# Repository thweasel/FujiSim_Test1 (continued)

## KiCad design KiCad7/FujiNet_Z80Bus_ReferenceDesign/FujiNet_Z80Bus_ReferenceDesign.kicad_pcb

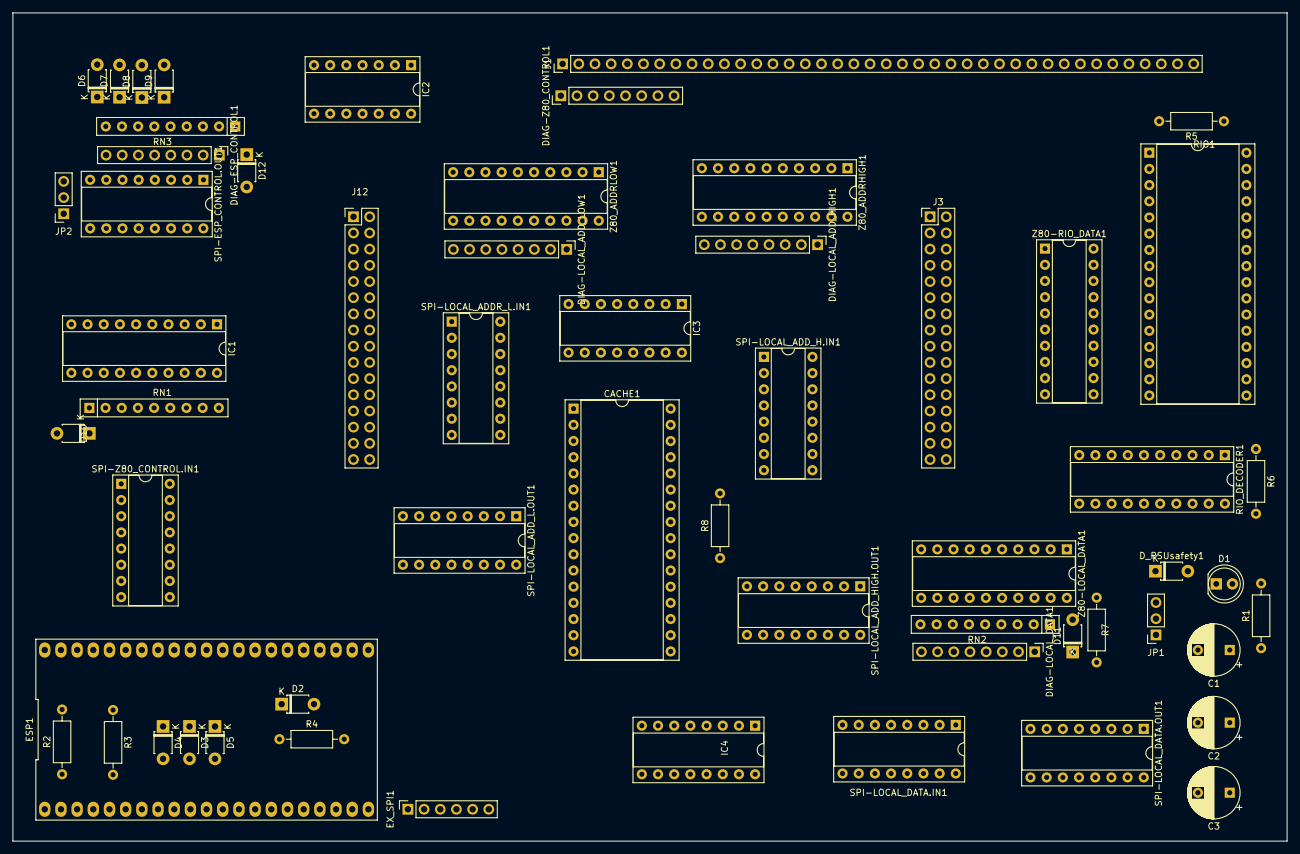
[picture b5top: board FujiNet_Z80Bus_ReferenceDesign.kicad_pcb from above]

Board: 2 copper layers, 200.0 x 130.0 mm, 58 parts (0 on the bottom side), 142 nets, no tracks yet.

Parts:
C1: 10 uf; CP_Radial_D8.0mm_P5.00mm
C2, C3: .1 uf; CP_Radial_D8.0mm_P5.00mm
CACHE1: AS6C1008-55PCN; DIP-32_W15.24mm_Socket
D1: POWER_LED; LED_D5.0mm
D2, D3, D4, D5, D6, D7, D8, D9, D10, D11, D12: 1N4148; D_T-1_P5.08mm_Horizontal
DIAG-ESP_CONTROL1: PinHeader_2.54mm; PinHeader_1x08_P2.54mm_Vertical
DIAG-LOCAL_ADD_HIGH1: PinHeader_2.54mm; PinHeader_1x08_P2.54mm_Vertical
DIAG-LOCAL_ADD_LOW1: PinHeader_2.54mm; PinHeader_1x08_P2.54mm_Vertical
DIAG-LOCAL_DATA1: PinHeader_2.54mm; PinHeader_1x08_P2.54mm_Vertical
DIAG-Z80_CONTROL1: PinHeader_2.54mm; PinHeader_1x08_P2.54mm_Vertical
D_PSUsafety1: 1N4148; D_T-1_P5.08mm_Horizontal
ESP1: FREENOVE_ESP32-WROVER-DEV
EX_SPI1: PinSocket_2.54mm; PinSocket_1x06_P2.54mm_Vertical
IC1: 74HC244N; DIP-20_W7.62mm_Socket
IC2: 74HC32N; DIP-14_W7.62mm_Socket
IC3, IC4: 74HC590N; DIP-16_W7.62mm_Socket
J1: DIAG-HOST_SYSTEM_BUS; PinHeader_1x40_P2.54mm_Vertical
J3, J12: Conn_02x12_Odd_Even; PinHeader_2x16_P2.54mm_Vertical
JP1: PINHD-POWER/RESET; PinSocket_1x03_P2.54mm_Vertical
JP2: PINHD-ADDR_FILTER; PinSocket_1x03_P2.54mm_Vertical
R1: 1K; R_Axial_DIN0207_L6.3mm_D2.5mm_P10.16mm_Horizontal
R2, R3, R4: 22K; R_Axial_DIN0207_L6.3mm_D2.5mm_P10.16mm_Horizontal
R5, R6, R7, R8: 10K; R_Axial_DIN0207_L6.3mm_D2.5mm_P10.16mm_Horizontal
RIO1: AS6C1008-55PCN; DIP-32_W15.24mm_Socket
RIO_DECODER1: 74HC245N; DIP-20_W7.62mm_Socket
RN1: LOCAL_CONTROL_BIAS; R_Array_SIP9
RN2, RN3: 4609M-101-103LF; R_Array_SIP9
SPI-ESP_CONTROL.OUT1: 74595N; DIP-16_W7.62mm_Socket
SPI-LOCAL_ADDR_L.IN1: 74HC165N; DIP-16_W7.62mm_Socket
SPI-LOCAL_ADD_H.IN1: 74HC165N; DIP-16_W7.62mm_Socket
SPI-LOCAL_ADD_HIGH.OUT1: 74595N; DIP-16_W7.62mm_Socket
SPI-LOCAL_ADD_L.OUT1: 74595N; DIP-16_W7.62mm_Socket
SPI-LOCAL_DATA.IN1: 74HC165N; DIP-16_W7.62mm_Socket
SPI-LOCAL_DATA.OUT1: 74595N; DIP-16_W7.62mm_Socket
SPI-Z80_CONTROL.IN1: 74HC165N; DIP-16_W7.62mm_Socket
Z80-LOCAL_DATA1, Z80-RIO_DATA1, Z80_ADDRHIGH1, Z80_ADDRLOW1: 74HC245N; DIP-20_W7.62mm_Socket

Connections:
+5V: C1.1, C2.1, C3.1, CACHE1.32 (VCC), D10.2 (A), D11.2 (A), D12.2 (A), D_PSUsafety1.2 (A), ESP1.20 (+5V), EX_SPI1.5, IC1.20 (VCC), IC2.14 (VCC), IC3.16 (VCC), IC4.16 (VCC), J12.21, R1.1, R2.2, R4.1, R5.1, R6.2, R7.2, R8.2, RIO1.32 (VCC), RIO_DECODER1.20 (VCC), SPI-ESP_CONTROL.OUT1.16 (VCC), SPI-LOCAL_ADDR_L.IN1.16 (VCC), SPI-LOCAL_ADD_H.IN1.16 (VCC), SPI-LOCAL_ADD_HIGH.OUT1.16 (VCC), SPI-LOCAL_ADD_L.OUT1.16 (VCC), SPI-LOCAL_DATA.IN1.16 (VCC), SPI-LOCAL_DATA.OUT1.16 (VCC), SPI-Z80_CONTROL.IN1.16 (VCC), Z80-LOCAL_DATA1.20 (VCC), Z80-RIO_DATA1.20 (VCC), Z80_ADDRHIGH1.20 (VCC), Z80_ADDRLOW1.20 (VCC)
/!ESP_HARDLOCK: IC1.19 (2OE), J12.20
/CACHE_CONTROL.A16: CACHE1.2 (A16), J3.12
/CACHE_CONTROL.CS: CACHE1.22 (CE#), J3.18
/CACHE_CONTROL.DATASTATUS+PERM_Z80_IORQ: IC3.11 (CPC), IC3.13 (CPR), J3.10
/CACHE_CONTROL.OE: CACHE1.24 (OE#), J3.16
/CACHE_CONTROL.WE: CACHE1.29 (WE#), J3.14
/CACHE_DATASTATUS: IC3.12 (~CE), IC3.14 (~OE), IC4.12 (~CE), IC4.14 (~OE), J3.9, R7.1, RIO_DECODER1.14 (B4)
/CACHE_SEL_0: CACHE1.4 (A12), RIO_DECODER1.18 (B0)
/CACHE_SEL_1: CACHE1.28 (A13), RIO_DECODER1.17 (B1)
/CACHE_SEL_2: CACHE1.3 (A14), RIO_DECODER1.16 (B2)
/CACHE_SEL_3: CACHE1.31 (A15), RIO_DECODER1.15 (B3)
/CORE_ESP32-WROVER/ESP_INT: D3.2 (A), D4.2 (A), D5.2 (A), ESP1.3 (GPIO36), R2.1, R3.2
/CORE_ESP32-WROVER/ESP_PULSE: ESP1.11 (GPIO27), IC2.1
/CORE_ESP32-WROVER/ESP_SPI_INT.CE: ESP1.31 (GPIO5), SPI-LOCAL_ADDR_L.IN1.15 (~CE), SPI-LOCAL_ADD_H.IN1.15 (~CE), SPI-LOCAL_DATA.IN1.15 (~CE), SPI-Z80_CONTROL.IN1.15 (~CE)
/CORE_ESP32-WROVER/ESP_SPI_INT.MISO: ESP1.33 (GPIO19), SPI-LOCAL_ADD_H.IN1.7 (~Q7)
/CORE_ESP32-WROVER/ESP_SPI_INT.MOSI: ESP1.39 (GPIO23), SPI-LOCAL_DATA.OUT1.14 (SER)
/CORE_ESP32-WROVER/ESP_SPI_INT.MR: R4.2, SPI-ESP_CONTROL.OUT1.10 (~SRCLR), SPI-LOCAL_ADD_HIGH.OUT1.10 (~SRCLR), SPI-LOCAL_ADD_L.OUT1.10 (~SRCLR), SPI-LOCAL_DATA.OUT1.10 (~SRCLR)
/CORE_ESP32-WROVER/ESP_SPI_INT.OE: ESP1.8 (GPIO33), SPI-ESP_CONTROL.OUT1.13 (~OE), SPI-LOCAL_ADD_HIGH.OUT1.13 (~OE), SPI-LOCAL_ADD_L.OUT1.13 (~OE)
/CORE_ESP32-WROVER/ESP_SPI_INT.PL: ESP1.9 (GPIO25), SPI-LOCAL_ADDR_L.IN1.1 (~PL), SPI-LOCAL_ADD_H.IN1.1 (~PL), SPI-LOCAL_DATA.IN1.1 (~PL), SPI-Z80_CONTROL.IN1.1 (~PL)
/CORE_ESP32-WROVER/ESP_SPI_INT.SCK: ESP1.32 (GPIO18), SPI-ESP_CONTROL.OUT1.11 (SRCLK), SPI-LOCAL_ADDR_L.IN1.2 (CP), SPI-LOCAL_ADD_H.IN1.2 (CP), SPI-LOCAL_ADD_HIGH.OUT1.11 (SRCLK), SPI-LOCAL_ADD_L.OUT1.11 (SRCLK), SPI-LOCAL_DATA.IN1.2 (CP), SPI-LOCAL_DATA.OUT1.11 (SRCLK), SPI-Z80_CONTROL.IN1.2 (CP)
/CORE_ESP32-WROVER/ESP_SPI_INT.STC: ESP1.10 (GPIO26), SPI-ESP_CONTROL.OUT1.12 (RCLK), SPI-LOCAL_ADD_HIGH.OUT1.12 (RCLK), SPI-LOCAL_ADD_L.OUT1.12 (RCLK), SPI-LOCAL_DATA.OUT1.12 (RCLK)
/CORE_ESP32-WROVER/EX_MISO: ESP1.13 (GPIO12), EX_SPI1.3
/CORE_ESP32-WROVER/EX_MOSI: ESP1.15 (GPIO13), EX_SPI1.4
/CORE_ESP32-WROVER/EX_SCK: ESP1.12 (GPIO14), EX_SPI1.2
/CORE_ESP32-WROVER/EX_SS: ESP1.25 (GPIO8), EX_SPI1.1
/CORE_ESP32-WROVER/SD_CARD_SS: ESP1.24 (GPIO15), ESP1.38 (GPIO22)
/ESP_CONTROL.BUSRQ: D9.1 (K), DIAG-ESP_CONTROL1.5, IC1.1 (1OE), J12.8, RN3.6 (R5), SPI-ESP_CONTROL.OUT1.4 (QE)
/ESP_CONTROL.IORQ: DIAG-ESP_CONTROL1.3, IC1.6 (1A2), IC1.13 (2A2), J12.4, RN3.4 (R3), SPI-ESP_CONTROL.OUT1.2 (QC)
/ESP_CONTROL.MEMRQ: DIAG-ESP_CONTROL1.4, IC1.8 (1A3), IC1.11 (2A3), J12.6, RN3.5 (R4), SPI-ESP_CONTROL.OUT1.3 (QD)
/ESP_CONTROL.NMI: D6.1 (K), DIAG-ESP_CONTROL1.8, RN3.9 (R8), SPI-ESP_CONTROL.OUT1.7 (QH)
/ESP_CONTROL.RD: DIAG-ESP_CONTROL1.1, IC1.2 (1A0), IC1.17 (2A0), RN3.2 (R1), SPI-ESP_CONTROL.OUT1.15 (QA)
/ESP_CONTROL.ROMCS: D7.1 (K), DIAG-ESP_CONTROL1.7, J12.10, RN3.8 (R7), SPI-ESP_CONTROL.OUT1.6 (QG)
/ESP_CONTROL.WAIT: D8.1 (K), DIAG-ESP_CONTROL1.6, RN3.7 (R6), SPI-ESP_CONTROL.OUT1.5 (QF)
/ESP_CONTROL.WR: DIAG-ESP_CONTROL1.2, IC2.2, J12.2, RN3.3 (R2), SPI-ESP_CONTROL.OUT1.1 (QB), SPI-LOCAL_DATA.OUT1.13 (~OE)
/ESP_HARDLOCK: ESP1.26 (GPIO2), J12.18
/ESP_ROMSEL_0: ESP1.23 (GPIO7), J12.14
/ESP_ROMSEL_1: ESP1.22 (GPIO6), J12.16
/ESP_ROM_WR_PROTECT: ESP1.28 (GPIO4), J12.12
/ESP_WAIT_RESET: ESP1.18 (GPIO11), J3.11
/IOCACHE-128K_ZXspectrum/CACHE_CE2: CACHE1.30 (CE2#), R8.1
/IORQ_FILTER_BIT: J3.1, JP2.2
/LOCAL_A0: CACHE1.12 (A0), DIAG-LOCAL_ADD_LOW1.1, IC3.15 (Q0), SPI-LOCAL_ADDR_L.IN1.11 (D0), SPI-LOCAL_ADD_L.OUT1.15 (QA), Z80_ADDRLOW1.18 (B0)
/LOCAL_A1: CACHE1.11 (A1), DIAG-LOCAL_ADD_LOW1.2, IC3.1 (Q1), SPI-LOCAL_ADDR_L.IN1.12 (D1), SPI-LOCAL_ADD_L.OUT1.1 (QB), Z80_ADDRLOW1.17 (B1)
/LOCAL_A2: CACHE1.10 (A2), DIAG-LOCAL_ADD_LOW1.3, IC3.2 (Q2), SPI-LOCAL_ADDR_L.IN1.13 (D2), SPI-LOCAL_ADD_L.OUT1.2 (QC), Z80_ADDRLOW1.16 (B2)
/LOCAL_A3: CACHE1.9 (A3), DIAG-LOCAL_ADD_LOW1.4, IC3.3 (Q3), SPI-LOCAL_ADDR_L.IN1.14 (D3), SPI-LOCAL_ADD_L.OUT1.3 (QD), Z80_ADDRLOW1.15 (B3)
/LOCAL_A4: CACHE1.8 (A4), DIAG-LOCAL_ADD_LOW1.5, IC3.4 (Q4), SPI-LOCAL_ADDR_L.IN1.3 (D4), SPI-LOCAL_ADD_L.OUT1.4 (QE), Z80_ADDRLOW1.14 (B4)
/LOCAL_A5: CACHE1.7 (A5), DIAG-LOCAL_ADD_LOW1.6, IC3.5 (Q5), SPI-LOCAL_ADDR_L.IN1.4 (D5), SPI-LOCAL_ADD_L.OUT1.5 (QF), Z80_ADDRLOW1.13 (B5)
/LOCAL_A6: CACHE1.6 (A6), DIAG-LOCAL_ADD_LOW1.7, IC3.6 (Q6), SPI-LOCAL_ADDR_L.IN1.5 (D6), SPI-LOCAL_ADD_L.OUT1.6 (QG), Z80_ADDRLOW1.12 (B6)
/LOCAL_A7: CACHE1.5 (A7), DIAG-LOCAL_ADD_LOW1.8, IC3.7 (Q7), SPI-LOCAL_ADDR_L.IN1.6 (D7), SPI-LOCAL_ADD_L.OUT1.7 (QH), Z80_ADDRLOW1.11 (B7)
/LOCAL_A8: CACHE1.27 (A8), DIAG-LOCAL_ADD_HIGH1.1, IC4.15 (Q0), SPI-LOCAL_ADD_H.IN1.11 (D0), SPI-LOCAL_ADD_HIGH.OUT1.15 (QA), Z80_ADDRHIGH1.18 (B0)
/LOCAL_A9: CACHE1.26 (A9), DIAG-LOCAL_ADD_HIGH1.2, IC4.1 (Q1), SPI-LOCAL_ADD_H.IN1.12 (D1), SPI-LOCAL_ADD_HIGH.OUT1.1 (QB), Z80_ADDRHIGH1.17 (B1)
/LOCAL_A10: CACHE1.25 (A11), DIAG-LOCAL_ADD_HIGH1.3, IC4.2 (Q2), SPI-LOCAL_ADD_H.IN1.13 (D2), SPI-LOCAL_ADD_HIGH.OUT1.2 (QC), Z80_ADDRHIGH1.16 (B2)
/LOCAL_A11: CACHE1.23 (A10), DIAG-LOCAL_ADD_HIGH1.4, IC4.3 (Q3), SPI-LOCAL_ADD_H.IN1.14 (D3), SPI-LOCAL_ADD_HIGH.OUT1.3 (QD), Z80_ADDRHIGH1.15 (B3)
/LOCAL_A12: DIAG-LOCAL_ADD_HIGH1.5, SPI-LOCAL_ADD_H.IN1.3 (D4), SPI-LOCAL_ADD_HIGH.OUT1.4 (QE), Z80_ADDRHIGH1.14 (B4)
/LOCAL_A13: DIAG-LOCAL_ADD_HIGH1.6, SPI-LOCAL_ADD_H.IN1.4 (D5), SPI-LOCAL_ADD_HIGH.OUT1.5 (QF), Z80_ADDRHIGH1.13 (B5)
/LOCAL_A14: DIAG-LOCAL_ADD_HIGH1.7, SPI-LOCAL_ADD_H.IN1.5 (D6), SPI-LOCAL_ADD_HIGH.OUT1.6 (QG), Z80_ADDRHIGH1.12 (B6)
/LOCAL_A15: DIAG-LOCAL_ADD_HIGH1.8, SPI-LOCAL_ADD_H.IN1.6 (D7), SPI-LOCAL_ADD_HIGH.OUT1.7 (QH), Z80_ADDRHIGH1.11 (B7)
/LOCAL_CONTROL.IORQ: IC1.14 (1Y2), J12.17, RN1.3 (R2)
/LOCAL_CONTROL.MEMRQ: IC1.12 (1Y3), J12.19, RN1.2 (R1)
/LOCAL_CONTROL.RD: IC1.18 (1Y0), J12.13, RN1.5 (R4)
/LOCAL_CONTROL.WR: IC1.16 (1Y1), J12.15, RN1.4 (R3)
/LOCAL_D0: CACHE1.13 (DQ0), DIAG-LOCAL_DATA1.1, RN2.2 (R1), SPI-LOCAL_DATA.IN1.11 (D0), SPI-LOCAL_DATA.OUT1.15 (QA), Z80-LOCAL_DATA1.18 (B0)
/LOCAL_D1: CACHE1.14 (DQ1), DIAG-LOCAL_DATA1.2, RN2.3 (R2), SPI-LOCAL_DATA.IN1.12 (D1), SPI-LOCAL_DATA.OUT1.1 (QB), Z80-LOCAL_DATA1.17 (B1)
/LOCAL_D2: CACHE1.15 (DQ2), DIAG-LOCAL_DATA1.3, RN2.4 (R3), SPI-LOCAL_DATA.IN1.13 (D2), SPI-LOCAL_DATA.OUT1.2 (QC), Z80-LOCAL_DATA1.16 (B2)
/LOCAL_D3: CACHE1.17 (DQ3), DIAG-LOCAL_DATA1.4, RN2.5 (R4), SPI-LOCAL_DATA.IN1.14 (D3), SPI-LOCAL_DATA.OUT1.3 (QD), Z80-LOCAL_DATA1.15 (B3)
/LOCAL_D4: CACHE1.18 (DQ4), DIAG-LOCAL_DATA1.5, RN2.6 (R5), SPI-LOCAL_DATA.IN1.3 (D4), SPI-LOCAL_DATA.OUT1.4 (QE), Z80-LOCAL_DATA1.14 (B4)
/LOCAL_D5: CACHE1.19 (DQ5), DIAG-LOCAL_DATA1.6, RN2.7 (R6), SPI-LOCAL_DATA.IN1.4 (D5), SPI-LOCAL_DATA.OUT1.5 (QF), Z80-LOCAL_DATA1.13 (B5)
/LOCAL_D6: CACHE1.20 (DQ6), DIAG-LOCAL_DATA1.7, RN2.8 (R7), SPI-LOCAL_DATA.IN1.5 (D6), SPI-LOCAL_DATA.OUT1.6 (QG), Z80-LOCAL_DATA1.12 (B6)
/LOCAL_D7: CACHE1.21 (DQ7), DIAG-LOCAL_DATA1.8, RN2.9 (R8), SPI-LOCAL_DATA.IN1.6 (D7), SPI-LOCAL_DATA.OUT1.7 (QH), Z80-LOCAL_DATA1.11 (B7)
/PERM_Z80_IORQ: J3.24, RIO_DECODER1.19 (CE)
/RIO-128K_ZXspectrum/RIO_CE2: R5.2, RIO1.30 (CE2#)
/RIO-128K_ZXspectrum/ROM_D0: RIO1.13 (DQ0), RIO_DECODER1.2 (A0), Z80-RIO_DATA1.18 (B0)
/RIO-128K_ZXspectrum/ROM_D1: RIO1.14 (DQ1), RIO_DECODER1.3 (A1), Z80-RIO_DATA1.17 (B1)
/RIO-128K_ZXspectrum/ROM_D2: RIO1.15 (DQ2), RIO_DECODER1.4 (A2), Z80-RIO_DATA1.16 (B2)
/RIO-128K_ZXspectrum/ROM_D3: RIO1.17 (DQ3), RIO_DECODER1.5 (A3), Z80-RIO_DATA1.15 (B3)
/RIO-128K_ZXspectrum/ROM_D4: RIO1.18 (DQ4), RIO_DECODER1.6 (A4), Z80-RIO_DATA1.14 (B4)
/RIO-128K_ZXspectrum/ROM_D5: RIO1.19 (DQ5), RIO_DECODER1.7 (A5), Z80-RIO_DATA1.13 (B5)
/RIO-128K_ZXspectrum/ROM_D6: RIO1.20 (DQ6), RIO_DECODER1.8 (A6), Z80-RIO_DATA1.12 (B6)
/RIO-128K_ZXspectrum/ROM_D7: RIO1.21 (DQ7), RIO_DECODER1.9 (A7), Z80-RIO_DATA1.11 (B7)
/RIO_CONTROL.A14: J3.17, RIO1.3 (A14)
/RIO_CONTROL.A15: J3.19, RIO1.31 (A15)
/RIO_CONTROL.OE: J3.23, RIO1.24 (OE#), Z80-RIO_DATA1.1 (A->B)
/RIO_CONTROL.WE: J3.21, RIO1.29 (WE#)
/SPI-Z80-BUS_ZXspectrum/ESP_CONTROL.WR+ESP_PULSE: IC1.4 (1A1), IC1.15 (2A1), IC2.3
/WAIT_IO: J3.7, RIO_DECODER1.13 (B5)
/Z80_A0: J1.18, JP2.3, RIO1.12 (A0), Z80_ADDRLOW1.2 (A0)
/Z80_A1: J1.17, RIO1.11 (A1), Z80_ADDRLOW1.3 (A1)
/Z80_A2: J1.16, RIO1.10 (A2), Z80_ADDRLOW1.4 (A2)
/Z80_A3: J1.15, RIO1.9 (A3), Z80_ADDRLOW1.5 (A3)
/Z80_A4: J1.14, RIO1.8 (A4), Z80_ADDRLOW1.6 (A4)
/Z80_A5: J1.13, RIO1.7 (A5), Z80_ADDRLOW1.7 (A5)
/Z80_A6: J1.12, RIO1.6 (A6), Z80_ADDRLOW1.8 (A6)
/Z80_A7: J1.11, RIO1.5 (A7), Z80_ADDRLOW1.9 (A7)
/Z80_A8: J1.26, RIO1.27 (A8), Z80_ADDRHIGH1.2 (A0)
/Z80_A9: J1.25, RIO1.26 (A9), Z80_ADDRHIGH1.3 (A1)
/Z80_A10: J1.24, RIO1.23 (A10), Z80_ADDRHIGH1.4 (A2)
/Z80_A11: J1.23, RIO1.25 (A11), Z80_ADDRHIGH1.5 (A3)
/Z80_A12: J1.22, RIO1.4 (A12), Z80_ADDRHIGH1.6 (A4)
/Z80_A13: J1.21, RIO1.28 (A13), Z80_ADDRHIGH1.7 (A5)
/Z80_A14: J1.20, J3.15, Z80_ADDRHIGH1.8 (A6)
/Z80_A15: J1.19, J3.13, Z80_ADDRHIGH1.9 (A7)
/Z80_BUS_CONTROL.Z80_ADD_DIR: J3.4, Z80_ADDRHIGH1.1 (A->B), Z80_ADDRLOW1.1 (A->B)
/Z80_BUS_CONTROL.Z80_ADD_OE: J3.2, Z80_ADDRHIGH1.19 (CE), Z80_ADDRLOW1.19 (CE)
/Z80_BUS_CONTROL.Z80_DATA_DIR: J3.6, Z80-LOCAL_DATA1.1 (A->B)
/Z80_BUS_CONTROL.Z80_DATA_OE: J3.8, Z80-LOCAL_DATA1.19 (CE)
/Z80_CONTROL.BUSACK: D5.1 (K), DIAG-Z80_CONTROL1.8, J1.9, SPI-Z80_CONTROL.IN1.5 (D6)
/Z80_CONTROL.BUSRQ: D9.2 (A), DIAG-Z80_CONTROL1.5, J1.5, J12.9, SPI-Z80_CONTROL.IN1.3 (D4)
/Z80_CONTROL.IORQ: DIAG-Z80_CONTROL1.3, IC1.7 (2Y2), J1.3, J12.5, SPI-Z80_CONTROL.IN1.13 (D2)
/Z80_CONTROL.MEMRQ: DIAG-Z80_CONTROL1.4, IC1.9 (2Y3), J1.4, J12.7, SPI-Z80_CONTROL.IN1.14 (D3)
/Z80_CONTROL.NMI: D6.2 (A), DIAG-Z80_CONTROL1.7, J1.7, SPI-Z80_CONTROL.IN1.6 (D7)
/Z80_CONTROL.RD: DIAG-Z80_CONTROL1.1, IC1.3 (2Y0), J1.1, J12.1, SPI-Z80_CONTROL.IN1.11 (D0)
/Z80_CONTROL.RESET: D2.2 (A), J1.10, JP1.1
/Z80_CONTROL.ROMCS: D7.2 (A), J1.8
/Z80_CONTROL.WAIT: D3.1 (K), D8.2 (A), DIAG-Z80_CONTROL1.6, J1.6, J12.11, SPI-Z80_CONTROL.IN1.4 (D5)
/Z80_CONTROL.WR: DIAG-Z80_CONTROL1.2, IC1.5 (2Y1), J1.2, J12.3, SPI-Z80_CONTROL.IN1.12 (D1)
/Z80_D0: J1.34, Z80-LOCAL_DATA1.2 (A0), Z80-RIO_DATA1.2 (A0)
/Z80_D1: J1.33, Z80-LOCAL_DATA1.3 (A1), Z80-RIO_DATA1.3 (A1)
/Z80_D2: J1.32, Z80-LOCAL_DATA1.4 (A2), Z80-RIO_DATA1.4 (A2)
/Z80_D3: J1.31, Z80-LOCAL_DATA1.5 (A3), Z80-RIO_DATA1.5 (A3)
/Z80_D4: J1.30, Z80-LOCAL_DATA1.6 (A4), Z80-RIO_DATA1.6 (A4)
/Z80_D5: J1.29, Z80-LOCAL_DATA1.7 (A5), Z80-RIO_DATA1.7 (A5)
/Z80_D6: J1.28, Z80-LOCAL_DATA1.8 (A6), Z80-RIO_DATA1.8 (A6)
/Z80_D7: J1.27, Z80-LOCAL_DATA1.9 (A7), Z80-RIO_DATA1.9 (A7)
/Z80_HARDLOCK: ESP1.4 (GPIO39), IC3.10 (~MRC), IC4.10 (~MRC), J3.20
/Z80_HARDLOCK_RESET: D4.1 (K), J3.3, RIO_DECODER1.12 (B6)
/Z80_HARDLOCK_SET: J3.5, RIO_DECODER1.11 (B7)
GND: C1.2, C2.2, C3.2, CACHE1.16 (VSS), D1.1 (K), ESP1.21 (GND), ESP1.34 (GND), ESP1.40 (GND), EX_SPI1.6, IC1.10 (GND), IC2.4, IC2.5, IC2.7 (GND), IC2.9, IC2.10, IC2.12, IC2.13, IC3.8 (GND), IC4.8 (GND), J1.40, J12.23, JP1.2, JP2.1, R3.1, RIO1.16 (VSS), RIO_DECODER1.10 (GND), SPI-ESP_CONTROL.OUT1.8 (GND), SPI-LOCAL_ADDR_L.IN1.8 (GND), SPI-LOCAL_ADD_H.IN1.8 (GND), SPI-LOCAL_ADD_HIGH.OUT1.8 (GND), SPI-LOCAL_ADD_L.OUT1.8 (GND), SPI-LOCAL_DATA.IN1.8 (GND), SPI-LOCAL_DATA.IN1.10 (DS), SPI-LOCAL_DATA.OUT1.8 (GND), SPI-Z80_CONTROL.IN1.8 (GND), Z80-LOCAL_DATA1.10 (GND), Z80-RIO_DATA1.10 (GND), Z80_ADDRHIGH1.10 (GND), Z80_ADDRLOW1.10 (GND)
unnamed: D1.2 (A), R1.2
unnamed: D2.1 (K), ESP1.35 (GPIO21)
unnamed: D10.1 (K), RN1.1 (common)
unnamed: D11.1 (K), RN2.1 (common)
unnamed: D12.1 (K), RN3.1 (common)
unnamed: D_PSUsafety1.1 (K), JP1.3
unnamed: IC3.9 (~RCO), IC4.11 (CPC), IC4.13 (CPR)
unnamed: R6.1, RIO_DECODER1.1 (A->B)
unnamed: SPI-ESP_CONTROL.OUT1.9 (QH'), SPI-LOCAL_ADD_L.OUT1.14 (SER)
unnamed: SPI-ESP_CONTROL.OUT1.14 (SER), SPI-LOCAL_DATA.OUT1.9 (QH')
unnamed: SPI-LOCAL_ADDR_L.IN1.10 (DS), SPI-Z80_CONTROL.IN1.7 (~Q7)
unnamed: SPI-LOCAL_ADDR_L.IN1.7 (~Q7), SPI-LOCAL_ADD_H.IN1.10 (DS)
unnamed: SPI-LOCAL_ADD_HIGH.OUT1.14 (SER), SPI-LOCAL_ADD_L.OUT1.9 (QH')
unnamed: SPI-LOCAL_DATA.IN1.7 (~Q7), SPI-Z80_CONTROL.IN1.10 (DS)

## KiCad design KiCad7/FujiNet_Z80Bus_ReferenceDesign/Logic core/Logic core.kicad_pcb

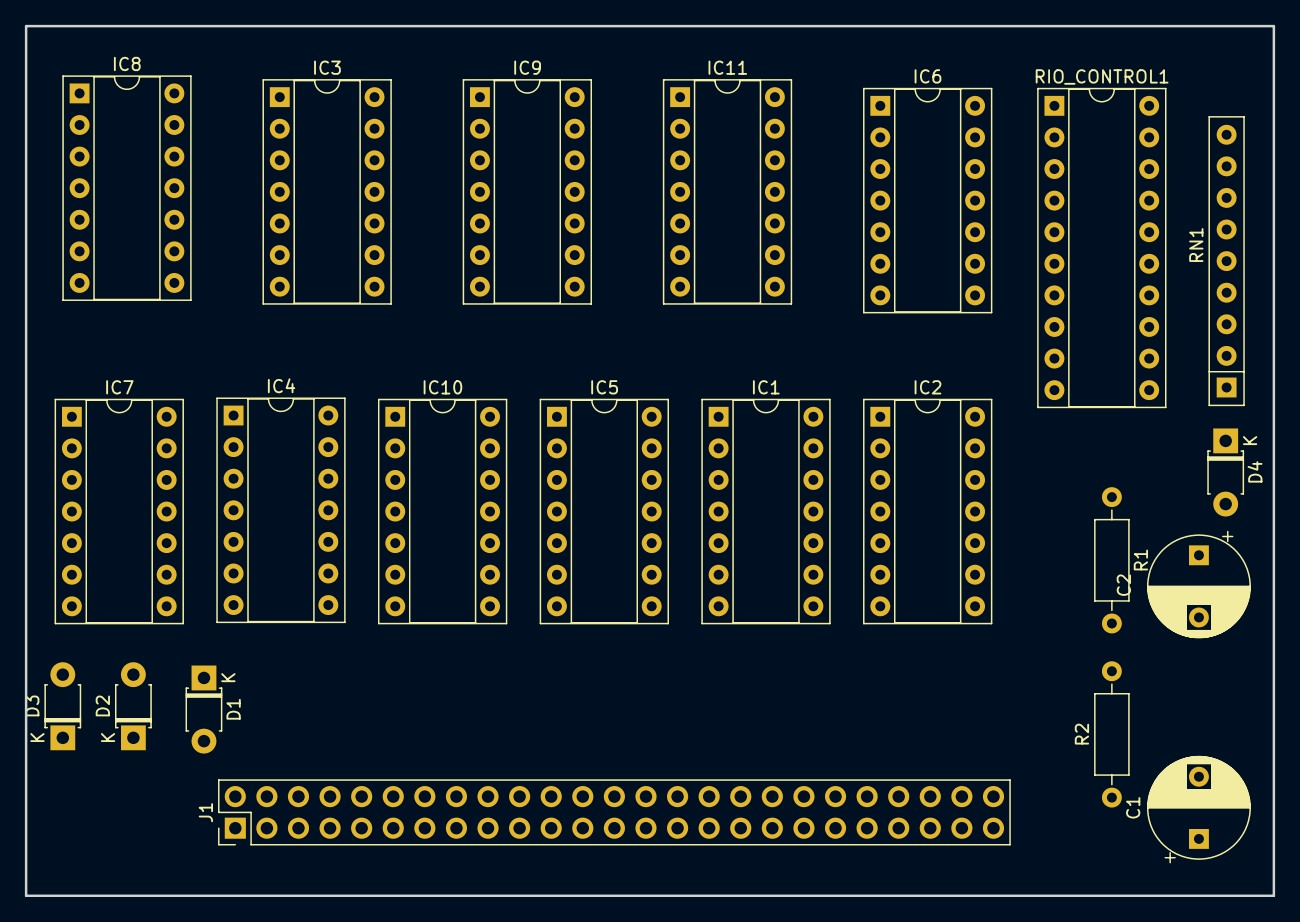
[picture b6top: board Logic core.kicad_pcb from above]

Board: 2 copper layers, 100.3 x 69.9 mm, 22 parts (0 on the bottom side), 60 nets, no tracks yet.

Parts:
C1, C2: 10UF; CP_Radial_D8.0mm_P5.00mm
D1, D2, D3, D4: 1N4148; D_T-1_P5.08mm_Horizontal
IC1: 7404N; DIP-14_W7.62mm_Socket
IC2, IC3, IC5, IC7, IC8, IC9: 74HC32N; DIP-14_W7.62mm_Socket
IC4: 7474N; DIP-14_W7.62mm_Socket
IC6, IC10, IC11: 74HC08N; DIP-14_W7.62mm_Socket
J1: Logic core connector; PinHeader_2x25_P2.54mm_Vertical
R1, R2: 22K; R_Axial_DIN0207_L6.3mm_D2.5mm_P10.16mm_Horizontal
RIO_CONTROL1: 74244N; DIP-20_W7.62mm_Socket
RN1: 4609M-101-103LF; R_Array_SIP9

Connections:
+5V: D4.2 (A), IC2.7 (GND), J1.46, R1.1, R2.1
/!ESP_HARDLOCK: IC1.2, J1.30
/!Z80_HARDLOCK: IC4.6 (~Q), J1.32
/CACHE_DATASTATUS: IC5.5, IC11.1, J1.35
/CLR_Z80_HARDLOCK: IC4.1 (~R), IC6.3
/ESP_CONTROL.BUSRQ: IC5.10, J1.9
/ESP_CONTROL.IORQ: IC6.5, J1.7
/ESP_CONTROL.MEMRQ: IC6.4, IC8.5, J1.8
/ESP_CONTROL.ROMCS: IC9.9, J1.10
/ESP_CONTROL.WR: IC7.9, J1.6
/ESP_HARDLOCK: IC1.1, IC3.9, IC5.2, J1.29
/ESP_IOD_CONFIG: IC5.8, IC8.4, IC9.1, IC9.5, IC10.5, IC10.12
/ESP_ROMSEL_0: J1.27, RIO_CONTROL1.13 (A2)
/ESP_ROMSEL_1: J1.28, RIO_CONTROL1.11 (A1)
/ESP_ROM_WR_PROTECT: IC9.13, J1.26
/ESP_WAIT_RESET: C1.1, IC4.13 (~R), J1.34, R1.2
/IORQ_FILTER_BIT: IC3.12, J1.39
/LOCAL_CONTROL.IORQ: IC11.2, J1.13
/LOCAL_CONTROL.MEMRQ: IC11.13, J1.14
/LOCAL_CONTROL.RD: IC11.10, J1.11
/LOCAL_CONTROL.WR: IC11.5, J1.12
/PERM_Z80_IORQ: IC3.11, IC5.4, IC7.1, IC7.5, IC8.13, IC10.1, IC10.4, IC11.12, J1.33
/PRE_Z80_HARDLOCK: IC4.4 (~S), IC5.3
/RIO CONTROL/RIO_CONTROL.A14: RIO_CONTROL1.9 (Y1), RIO_CONTROL1.18 (Y1), RN1.5
/RIO CONTROL/RIO_CONTROL.A15: RIO_CONTROL1.7 (Y2), RIO_CONTROL1.16 (Y2), RN1.4
/RIO CONTROL/RIO_CONTROL.A16: IC10.6, IC10.10, RIO_CONTROL1.1 (G)
/RIO CONTROL/RIO_CONTROL.OE: RIO_CONTROL1.3 (Y4), RIO_CONTROL1.12 (Y4), RN1.2
/RIO CONTROL/RIO_CONTROL.ROM_RDY: IC9.8, IC10.13, RIO_CONTROL1.19 (G)
/RIO CONTROL/RIO_CONTROL.WE: RIO_CONTROL1.5 (Y3), RIO_CONTROL1.14 (Y3), RN1.3
/RIO CONTROL/ROM_WR_PROTECT+Z80_WR: IC9.11, RIO_CONTROL1.15 (A3)
/RIO CONTROL/Z80_RD+ESP_IOD_CONFIG+PERM_Z80_IORQ: IC10.3, RIO_CONTROL1.8 (A4)
/RIO CONTROL/Z80_WR+ESP_IOD_CONFIG: IC9.3, RIO_CONTROL1.6 (A3)
/WAIT_IO: IC1.9, J1.36
/Z80 BUS CONTROL/Z80_ADD_CONNECT: D2.2 (A), IC8.1
/Z80 BUS CONTROL/Z80_DATA_CONNECT: D3.2 (A), IC7.10, IC8.12
/Z80_A14: J1.41, RIO_CONTROL1.4 (A2)
/Z80_A15: J1.40, RIO_CONTROL1.2 (A1)
/Z80_CONTROL.BUSRQ: D2.1 (K), D3.1 (K), J1.4
/Z80_CONTROL.MEMRQ: IC9.10, J1.3
/Z80_CONTROL.RD: IC7.4, IC9.4, IC11.9, J1.1, RIO_CONTROL1.17 (A4)
/Z80_CONTROL.WAIT: D1.2 (A), J1.5
/Z80_CONTROL.WR: IC9.2, IC9.12, IC11.4, J1.2
/Z80_HARDLOCK: IC4.5 (Q), J1.31
/Z80_HARDLOCK_RESET: IC1.5, J1.38
/Z80_HARDLOCK_SET: IC1.3, J1.37
GND: C1.2, C2.2, IC2.14 (VCC), J1.47
unnamed: C2.1, IC6.1, R2.2
unnamed: D1.1 (K), IC4.8 (~Q)
unnamed: D4.1 (K), RN1.1
unnamed: IC1.4, IC5.1
unnamed: IC1.6, IC6.2
unnamed: IC1.10, IC5.9
unnamed: IC1.11, IC6.6
unnamed: IC3.8, IC3.13
unnamed: IC1.8, IC4.10 (~S)
unnamed: IC7.3, IC8.2
unnamed: IC7.6, IC8.9
unnamed: IC7.8, IC8.10
unnamed: IC9.6, IC10.2
unnamed: IC10.9, IC10.11

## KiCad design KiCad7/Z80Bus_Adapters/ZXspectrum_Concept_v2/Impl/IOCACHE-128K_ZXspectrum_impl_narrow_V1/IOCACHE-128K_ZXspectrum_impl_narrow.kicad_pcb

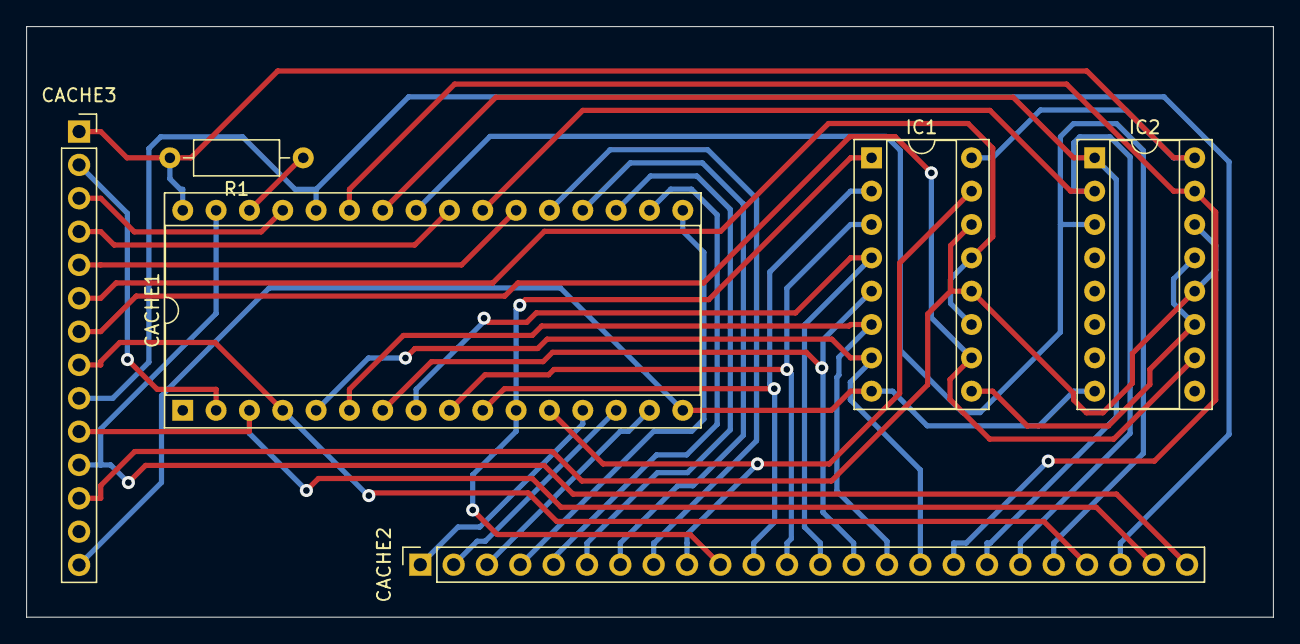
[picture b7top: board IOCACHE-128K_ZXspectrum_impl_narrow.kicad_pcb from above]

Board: 2 copper layers, 95.0 x 45.0 mm, 6 parts (0 on the bottom side), 35 nets.

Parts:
CACHE1: AS6C1008-55PCN; DIP-32_W15.24mm_Socket
CACHE2: Conn_01x24_Socket; PinSocket_1x24_P2.54mm_Vertical
CACHE3: Conn_01x14_Socket; PinSocket_1x14_P2.54mm_Vertical
IC1, IC2: 74HC590N; DIP-16_W7.62mm_Socket
R1: 10K; R_Axial_DIN0207_L6.3mm_D2.5mm_P10.16mm_Horizontal

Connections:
+5V: CACHE1.32 (VCC), CACHE3.1, IC1.16 (VCC), IC2.16 (VCC), R1.2
/IOCACHE-128K_ZXspectrum/CACHE_CE2: CACHE1.30 (CE2#), R1.1
/IOCACHE-128K_ZXspectrum/CACHE_CONTROL.A16: CACHE1.2 (A16), CACHE3.2
/IOCACHE-128K_ZXspectrum/CACHE_CONTROL.CS: CACHE1.22 (CE#), CACHE3.5
/IOCACHE-128K_ZXspectrum/CACHE_CONTROL.DATASTATUS+PERM_Z80_IORQ: CACHE3.6, IC1.11 (CPC), IC1.13 (CPR)
/IOCACHE-128K_ZXspectrum/CACHE_CONTROL.OE: CACHE1.24 (OE#), CACHE3.4
/IOCACHE-128K_ZXspectrum/CACHE_CONTROL.WE: CACHE1.29 (WE#), CACHE3.3
/IOCACHE-128K_ZXspectrum/CACHE_DATASTATUS: CACHE3.12, IC1.12 (~CE), IC1.14 (~OE), IC2.12 (~CE), IC2.14 (~OE)
/IOCACHE-128K_ZXspectrum/LOCAL_A0: CACHE1.12 (A0), CACHE2.9, IC1.15 (Q0)
/IOCACHE-128K_ZXspectrum/LOCAL_A1: CACHE1.11 (A1), CACHE2.10, IC1.1 (Q1)
/IOCACHE-128K_ZXspectrum/LOCAL_A2: CACHE1.10 (A2), CACHE2.11, IC1.2 (Q2)
/IOCACHE-128K_ZXspectrum/LOCAL_A3: CACHE1.9 (A3), CACHE2.12, IC1.3 (Q3)
/IOCACHE-128K_ZXspectrum/LOCAL_A4: CACHE1.8 (A4), CACHE2.13, IC1.4 (Q4)
/IOCACHE-128K_ZXspectrum/LOCAL_A5: CACHE1.7 (A5), CACHE2.14, IC1.5 (Q5)
/IOCACHE-128K_ZXspectrum/LOCAL_A6: CACHE1.6 (A6), CACHE2.15, IC1.6 (Q6)
/IOCACHE-128K_ZXspectrum/LOCAL_A7: CACHE1.5 (A7), CACHE2.16, IC1.7 (Q7)
/IOCACHE-128K_ZXspectrum/LOCAL_A8: CACHE1.27 (A8), CACHE2.17, IC2.15 (Q0)
/IOCACHE-128K_ZXspectrum/LOCAL_A9: CACHE1.26 (A9), CACHE2.18, IC2.1 (Q1)
/IOCACHE-128K_ZXspectrum/LOCAL_A10: CACHE1.23 (A10), CACHE2.19, IC2.2 (Q2)
/IOCACHE-128K_ZXspectrum/LOCAL_A11: CACHE1.25 (A11), CACHE2.20, IC2.3 (Q3)
/IOCACHE-128K_ZXspectrum/LOCAL_A12: CACHE1.4 (A12), CACHE2.21, CACHE3.8
/IOCACHE-128K_ZXspectrum/LOCAL_A13: CACHE1.28 (A13), CACHE2.22, CACHE3.9
/IOCACHE-128K_ZXspectrum/LOCAL_A14: CACHE1.3 (A14), CACHE2.23, CACHE3.10
/IOCACHE-128K_ZXspectrum/LOCAL_A15: CACHE1.31 (A15), CACHE2.24, CACHE3.11
/IOCACHE-128K_ZXspectrum/LOCAL_D0: CACHE1.13 (DQ0), CACHE2.1
/IOCACHE-128K_ZXspectrum/LOCAL_D1: CACHE1.14 (DQ1), CACHE2.2
/IOCACHE-128K_ZXspectrum/LOCAL_D2: CACHE1.15 (DQ2), CACHE2.3
/IOCACHE-128K_ZXspectrum/LOCAL_D3: CACHE1.17 (DQ3), CACHE2.4
/IOCACHE-128K_ZXspectrum/LOCAL_D4: CACHE1.18 (DQ4), CACHE2.5
/IOCACHE-128K_ZXspectrum/LOCAL_D5: CACHE1.19 (DQ5), CACHE2.6
/IOCACHE-128K_ZXspectrum/LOCAL_D6: CACHE1.20 (DQ6), CACHE2.7
/IOCACHE-128K_ZXspectrum/LOCAL_D7: CACHE1.21 (DQ7), CACHE2.8
/IOCACHE-128K_ZXspectrum/Z80_HARDLOCK: CACHE3.7, IC1.10 (~MRC), IC2.10 (~MRC)
GND: CACHE1.16 (VSS), CACHE3.14, IC1.8 (GND), IC2.8 (GND)
unnamed: IC1.9 (~RCO), IC2.11 (CPC), IC2.13 (CPR)
